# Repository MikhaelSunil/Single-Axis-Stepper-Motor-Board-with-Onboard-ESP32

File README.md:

# 🧭 SINGLE-AXIS STEPPER MOTOR CONTROLLER BOARD WITH ESP32

This project is a **compact single-axis stepper motor controller board** centered on an **ESP32 microcontroller** and an integrated **DRV8825 stepper motor driver**.  
The board accepts a 12 V motor supply, provides regulated 5 V and 3.3 V outputs, supports mechanical limit switches for homing and end-stop safety, and enables both **Wi-Fi** and **Bluetooth** remote control.

---
**
**
## 🎯 OBJECTIVE
To develop a **modular, intelligent, single-axis motion control board** that integrates an **ESP32** microcontroller and **DRV8825** stepper driver with built-in **limit switch** support — suitable for automation and robotics applications.

---

## ⚙️ DESIGN OVERVIEW
The board integrates three main subsystems:

1. **Microcontroller Unit (ESP32-DevkitC)**  
   Handles motor control and limit switch detection.
2. **Power Regulation System**  
   Uses dual **LM2596** buck converters for 12 V → 5 V and 3.3 V rails.
3. **Motor Driver Subsystem (DRV8825)**  
   Provides microstepping control, efficient current regulation, and protection features.

---

## 🧠 MICROCONTROLLER – ESP32 DEVKITC
The **ESP32** was selected over alternatives like the **STM32**, **SAMD**, and **RP2040** for its:
- Superior processing power  
- Integrated **Wi-Fi** and **Bluetooth**  
- Wide GPIO accessibility  
- Compatibility with STEP/DIR motor control interfaces  

---

## ⚡ STEPPER MOTOR DRIVER – DRV8825
**Texas Instruments DRV8825** offers key advantages:
- **Wide Voltage Range:** 8.2 V – 45 V  
- **High Current:** Up to 2.2 A per phase  
- **Microstepping:** Up to 1/32 steps for fine resolution  
- **Built-in Protections:** Over-temperature, over-current, and short-to-ground  
- **Ease of Control:** Simple STEP/DIR interface  

---

## 🔩 STEP-SIZE SELECTION FEATURE
The board provides **microstep selection jumpers**, allowing dynamic configuration from **full-step to 1/32-step** without changing the software — ideal for performance and precision tuning.

---

## 🔋 POWER SUPPLY DESIGN

### **Input**
- 12 V DC main supply (motor and logic source)

### **Regulated Outputs**
- **LM2596T (5 V Output)** – High-efficiency regulator (>80%), powers peripherals and logic.  
- **LM2596S (3.3 V Output)** – Dedicated rail for step-selection jumpers and pull-ups with LC filtering.

---

## 🏁 LIMIT SWITCH AND HOMING INTEGRATION
Includes two **mechanical limit switches** with pull-up resistors for reliable **homing** and **end-stop** detection.  
Applications include **CNC**, **linear actuators**, and **positioning systems**.

---

## 🧾 PINOUT DESCRIPTION

| Signal      | ESP32 GPIO | I/O     | Connected Component         | Description |
|--------------|-------------|---------|------------------------------|-------------|
| **DIR_PIN**  | GPIO 19     | Output  | DRV8825 DIR                 | Motor rotation direction (HIGH = Forward, LOW = Reverse) |
| **STEP_PIN** | GPIO 18     | Output  | DRV8825 STEP                | Step pulse signal for motor movement |
| **EN_PIN**   | GPIO 21     | Output  | DRV8825 ENABLE              | Active LOW enable/disable for driver output |
| **LIMIT_MIN**| GPIO 32     | Input   | Mechanical Limit Switch (Home) | Detects home position (LOW = Pressed) |
| **LIMIT_MAX**| GPIO 33     | Input   | Mechanical Limit Switch (End)  | Detects maximum travel (LOW = Pressed) |

---

## 💡 NOVELTY & KEY FEATURES
- **Unified Architecture:** ESP32 + DRV8825 + Power Regulation on a single PCB  
- **Full GPIO Access:** Enables sensor, relay, and IoT expansion  
- **Dual Power Path:** Independent LM2596 converters reduce EMI  
- **OTA Upgradability:** Firmware updates over Wi-Fi  
- **Scalable Design:** Multiple boards networked for multi-axis systems  

---

## 🚀 APPLICATIONS
- 🧰 **CNC Machines & 3D Printers** – Precision motion control with homing  
- 🤖 **Autonomous Robotics** – For actuators, camera sliders, robot joints  
- 🌐 **IoT Mechatronics Systems** – Wi-Fi/BLE remote stepper control  
- ⚗️ **Smart Automation & Lab Equipment** – Syringe pumps, optical stages  
- 🎓 **Educational / Research Prototyping** – Open, reconfigurable motion control platform  

---

## 🧩 LICENSE
This project is open-source under the **MIT License**.  
You are free to use, modify, and distribute it with attribution.

---

## 👨‍🔧 Author
**Mikhael Sunil**  
Embedded Systems & Robotics Engineer  
📧 [LinkedIn](https://www.linkedin.com/in/mikhaelsunil) • 🌐 [GitHub](https://github.com/mikhaelsunil)

---

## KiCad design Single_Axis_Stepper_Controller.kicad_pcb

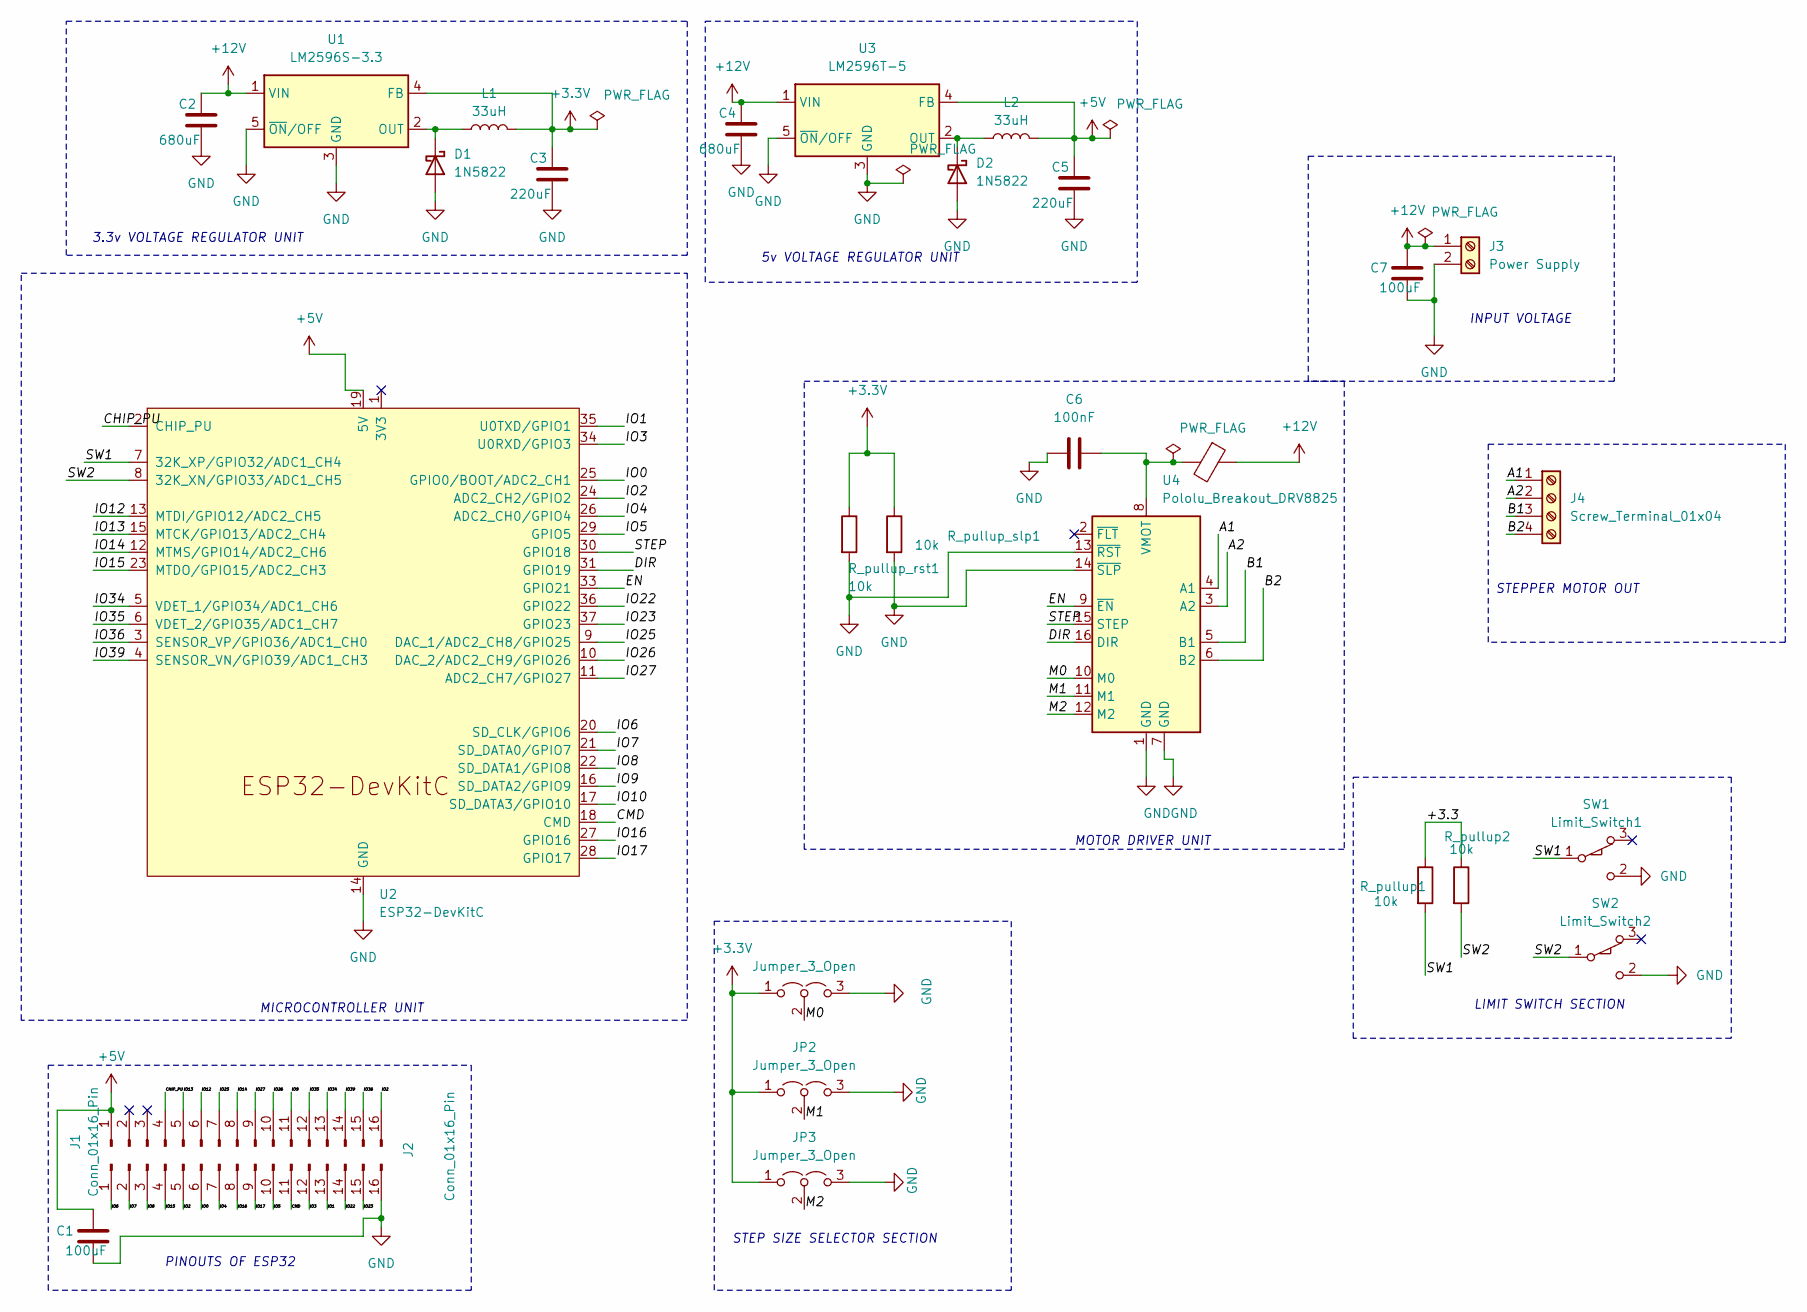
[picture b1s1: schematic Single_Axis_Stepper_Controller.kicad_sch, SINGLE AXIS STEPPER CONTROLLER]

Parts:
C1: 100uF; CP_Radial_D6.3mm_P2.50mm
C2, C4: 680uF; CP_Radial_D18.0mm_P7.50mm
C3: 220uF; CP_Radial_D18.0mm_P7.50mm
C5: 220uF; CP_Radial_D12.5mm_P2.50mm
C6: 100nF; CP_Radial_D7.5mm_P2.50mm
C7: 100uF; CP_Radial_D12.5mm_P5.00mm
D1, D2: 1N5822; D_DO-201AD_P15.24mm_Horizontal
FB1: FerriteBead; LairdTech_28C0236-0JW-10
J1, J2: Conn_01x16_Pin; PinHeader_1x16_P2.54mm_Vertical
J3: Power Supply; TerminalBlock_MaiXu_MX126-5.0-02P_1x02_P5.00mm
J4: Screw_Terminal_01x04; TerminalBlock_MaiXu_MX126-5.0-04P_1x04_P5.00mm
JP1, JP2, JP3: Jumper_3_Open; SolderJumper-3_P1.3mm_Open_Pad1.0x1.5mm
L1, L2: 33uH; L_Axial_L5.0mm_D3.6mm_P10.00mm_Horizontal_Murata_BL01RN1A2A2
R_pullup1, R_pullup2: 10k; R_Axial_DIN0207_L6.3mm_D2.5mm_P15.24mm_Horizontal
R_pullup_rst1: 10k; R_Axial_DIN0207_L6.3mm_D2.5mm_P15.24mm_Horizontal
R_pullup_slp1: 10k; R_Axial_DIN0207_L6.3mm_D2.5mm_P15.24mm_Horizontal
SW1: Limit_Switch1; SW_XKB_DM1-16UP-1
SW2: Limit_Switch2; SW_XKB_DM1-16UP-1
U1: LM2596S-3.3; TO-263-5_TabPin3
U2: ESP32-DevKitC
U3: LM2596T-5; TO-220-5_P3.4x3.7mm_StaggerOdd_Lead3.8mm_Vertical
U4: Pololu_Breakout_DRV8825; Pololu_Breakout-16_15.2x20.3mm

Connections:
+3.3V: C3.1, JP1.1 (A), JP2.1 (A), JP3.1 (A), L1.2, R_pullup_rst1.1, R_pullup_slp1.1, U1.4 (FB)
+5V: C1.1, C5.1, J1.1, L2.2, U2.19 (5V), U3.4 (FB)
+12V: C2.1, C4.1, C7.1, FB1.1, J3.1, U1.1 (VIN), U3.1 (VIN)
/+3.3: R_pullup1.1, R_pullup2.1
/A1: J4.1, U4.4 (A1)
/A2: J4.2, U4.3 (A2)
/B1: J4.3, U4.5 (B1)
/B2: J4.4, U4.6 (B2)
/CHIP_PU: J1.4, U2.2 (CHIP_PU)
/CMD: J2.11, U2.18 (CMD)
/DIR: U2.31 (GPIO19), U4.16 (DIR)
/EN: U2.33 (GPIO21), U4.9 (~EN)
/IO0: J2.6, U2.25 (GPIO0/BOOT/ADC2_CH1)
/IO1: J2.13, U2.35 (U0TXD/GPIO1)
/IO2: J1.16, J2.5, U2.24 (ADC2_CH2/GPIO2)
/IO3: J2.12, U2.34 (U0RXD/GPIO3)
/IO4: J2.7, U2.26 (ADC2_CH0/GPIO4)
/IO5: J2.10, U2.29 (GPIO5)
/IO6: J2.1, U2.20 (SD_CLK/GPIO6)
/IO7: J2.2, U2.21 (SD_DATA0/GPIO7)
/IO8: J2.3, U2.22 (SD_DATA1/GPIO8)
/IO9: J1.11, U2.16 (SD_DATA2/GPIO9)
/IO10: U2.17 (SD_DATA3/GPIO10)
/IO12: J1.6, U2.13 (MTDI/GPIO12/ADC2_CH5)
/IO13: J1.5, U2.15 (MTCK/GPIO13/ADC2_CH4)
/IO14: J1.8, U2.12 (MTMS/GPIO14/ADC2_CH6)
/IO15: J2.4, U2.23 (MTDO/GPIO15/ADC2_CH3)
/IO16: J2.8, U2.27 (GPIO16)
/IO17: J2.9, U2.28 (GPIO17)
/IO22: J2.14, U2.36 (GPIO22)
/IO23: J2.15, U2.37 (GPIO23)
/IO25: J1.7, U2.9 (DAC_1/ADC2_CH8/GPIO25)
/IO26: J1.10, U2.10 (DAC_2/ADC2_CH9/GPIO26)
/IO27: J1.9, U2.11 (ADC2_CH7/GPIO27)
/IO34: J1.13, U2.5 (VDET_1/GPIO34/ADC1_CH6)
/IO35: J1.12, U2.6 (VDET_2/GPIO35/ADC1_CH7)
/IO36: J1.15, U2.3 (SENSOR_VP/GPIO36/ADC1_CH0)
/IO39: J1.14, U2.4 (SENSOR_VN/GPIO39/ADC1_CH3)
/M0: JP1.2 (C), U4.10 (M0)
/M1: JP2.2 (C), U4.11 (M1)
/M2: JP3.2 (C), U4.12 (M2)
/STEP: U2.30 (GPIO18), U4.15 (STEP)
/SW1: R_pullup1.2, SW1.1 (A), U2.7 (32K_XP/GPIO32/ADC1_CH4)
/SW2: R_pullup2.2, SW2.1 (A), U2.8 (32K_XN/GPIO33/ADC1_CH5)
GND: C1.2, C2.2, C3.2, C4.2, C5.2, C6.2, C7.2, D1.2 (A), D2.2 (A), J2.16, J3.2, JP1.3 (B), JP2.3 (B), JP3.3 (B), R_pullup_rst1.2, R_pullup_slp1.2, SW1.2 (B), SW2.2 (B), U1.3 (GND), U1.5 (~ON/OFF), U2.14 (GND), U2.32 (GND), U2.38 (GND), U3.3 (GND), U3.5 (~ON/OFF), U4.1 (GND), U4.7 (GND), U4.13 (~RST), U4.14 (~SLP)
unnamed: D1.1 (K), L1.1, U1.2 (OUT)
unnamed: D2.1 (K), L2.1, U3.2 (OUT)
unnamed: C6.1, FB1.2, U4.8 (VMOT)

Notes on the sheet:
MICROCONTROLLER UNIT
STEPPER MOTOR OUT
3.3v VOLTAGE REGULATOR UNIT
LIMIT SWITCH SECTION
PINOUTS OF ESP32
5v VOLTAGE REGULATOR UNIT
STEP SIZE SELECTOR SECTION
MOTOR DRIVER UNIT
INPUT VOLTAGE

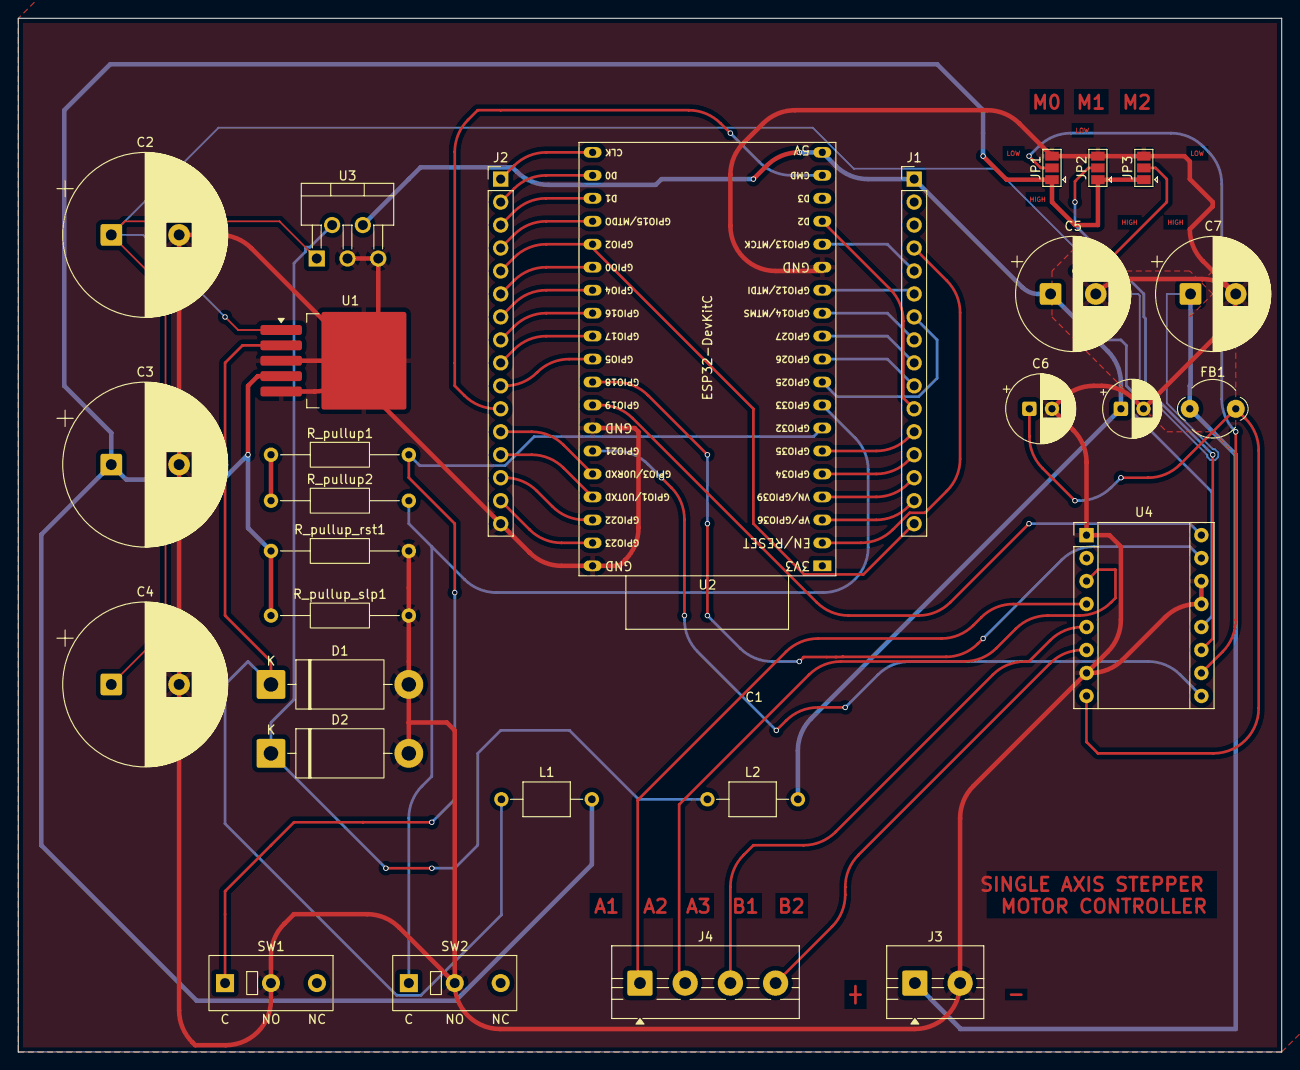
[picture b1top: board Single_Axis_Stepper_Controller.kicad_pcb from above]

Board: 2 copper layers, 139.7 x 114.3 mm, 29 parts (0 on the bottom side), 47 nets.

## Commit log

2025-10-17 Initial commit - added KiCad project and controller code
2025-10-23 Revise README for single-axis stepper motor controller
    Updated README to enhance project description and features.
